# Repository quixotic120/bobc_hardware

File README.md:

Fork of bobc’s hardware projects branch for my variant of Ramps-FD. See readme inside Ramps-FD for more info

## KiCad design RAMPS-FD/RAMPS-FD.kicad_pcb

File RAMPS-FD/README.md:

remix of ramps-fd; originally by bobc: https://github.com/bobc/bobc_hardware/tree/master/RAMPS-FD

edit: got the first rev of the board back but there were some clearance issues and a few errors in the schematic. these have been revised and rev 2 is on order. I have to again promote bayareacircuits - the price is unbeatable if you have a .edu email and the boards are of good quality. The solder mask leaves a bit to be desired but for the cost I can’t complain, especially when UV curable mask for touchups can be had on eBay for next to nothing. I have also began configuring a version of repetier to accommodate the changes and additions in the pinout; this is also on my github

as of now this is untested! board on order; will test very soon

based on v2.a - wasn't able to find anything but the flawed v1 for sale and other due/32-bit electronics didn't support what I want to do. So I made my own
I dont believe I changed any pinouts so the ramps-fd v2.a selection in repetier should cover this board as well. I'll certainly double check this

changes made - 
board layout is completely new 

added dedicated 5v supply on board. I'm using a murata dc-dc converter that is excellent but a bit expensive (7-10 bucks); however it is pin compatible with any 7805 for lower cost (but significantly more heat). Also left in the option to use the due's 5v out but it's not sufficient for the extras I want

integrated the LCD connector board. Hate having an extra board hanging off and never use the ports for anything else. Lose several aux ports as a result.

6 stepper support (x,y,z,e0,e1,e2). Drivers are integrated to the board and are TMC2100/2130 (either will work). For the most part cooling should be okay but the board is a bit tight so some can't have all of their vias for heat dispersal. I don't know how bad this is but compared to the crap cooling on most stepper drivers I'm assuming it will be okay. I suck at PCB layout so this could probably be significantly improved. also could probably further remix to utilize DRV8825/a4988 for the extruders as I'd imagine the TMC drivers dont have much of a benefit there. This wouldnt necessarily make anything easier but would lower the cost of the board by a few dollars and be slightly easier to solder

added a second header for z axis in parallel for machines with two z steppers

with the exception of very few parts almost everything has been moved to SMD parts. Off the top of my head I'm pretty sure the only through hole components are the various pin headers for connection to Due, servos, lcd, etc, jacks for auto mini blade fuses, and the connectors for power connections. Ton of vias though so if you plan to manufacture this get ready for a serious headache.

adding a layer could probably improve the layout significantly but I'm shooting for very cheap manufacture. I have placed an order via http://store.bayareacircuits.com/student-special/ (need a student email (e.g. .edu) for discount) and with shipping and tax it was around 40 bucks for the prototype. Will report when it arrives. 

otherwise it is available via [oshpark](https://oshpark.com/shared_projects/LaipPQTx) @ 164.65+shipping for 3 (min order, ~55 per board) as of 3/30/16

GPLv3

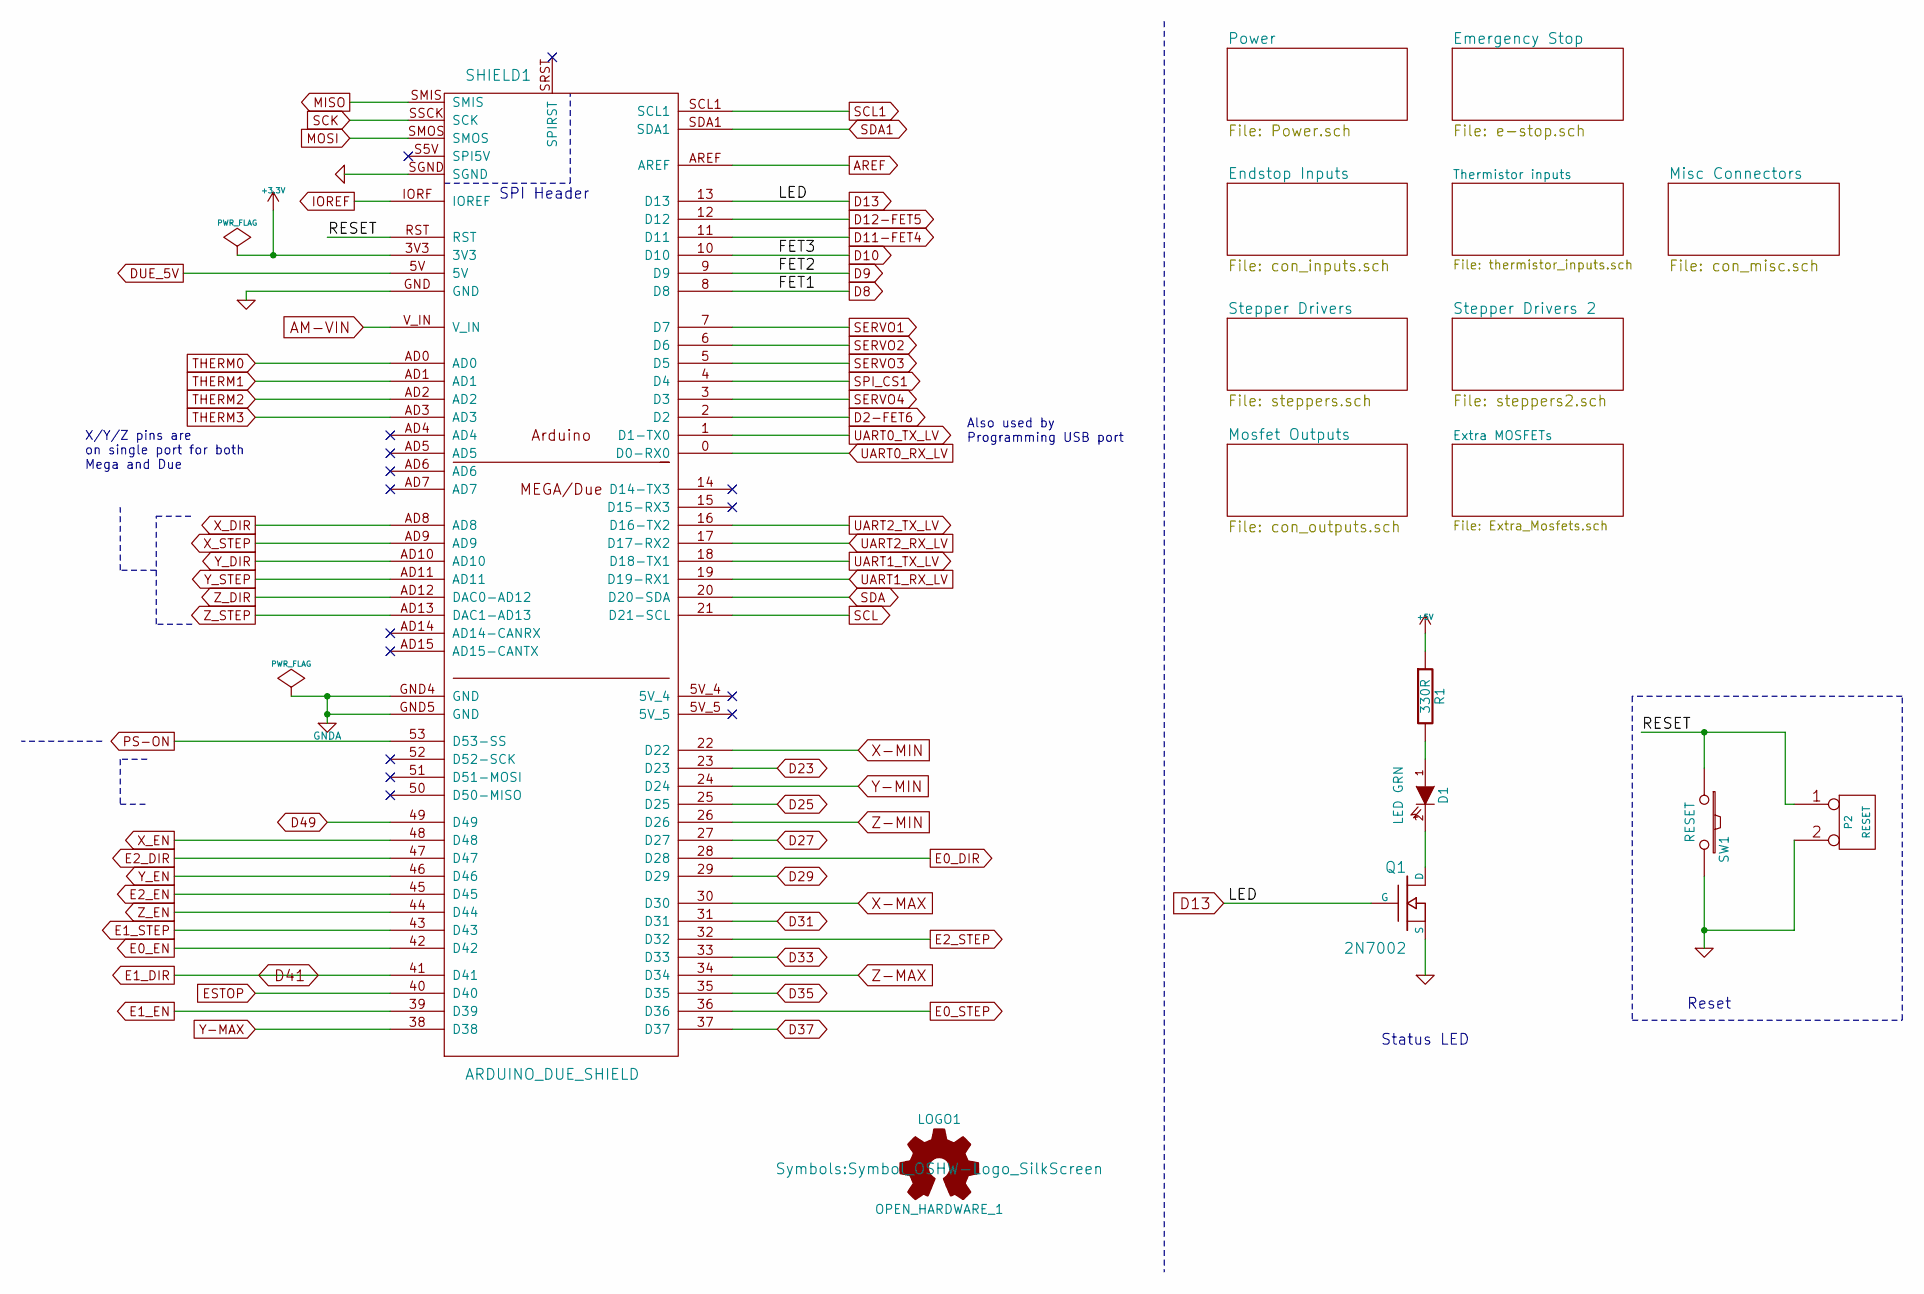
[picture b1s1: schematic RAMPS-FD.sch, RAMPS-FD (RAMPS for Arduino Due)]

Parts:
D1: LED GRN; LED_0805
LOGO1: OPEN_HARDWARE_1; Symbol_OSHW-Logo_SilkScreen
P2: RESET; Pin_Header_Straight_1x02
Q1: 2N7002; SOT-23_GDS
R1: 330R; R_0805
SHIELD1: ARDUINO_DUE_SHIELD; ARDUINO_DUE_RAMPS_SHIELD
SW1: RESET; SW_PUSH_SMALL

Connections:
+3V3: SHIELD1.3V3
/RESET: P2.1, SHIELD1.RST, SW1.1
AM-VIN: SHIELD1.V_IN; also elsewhere on the board
D2-FET6: SHIELD1.2 (D2); also elsewhere on the board
D8: SHIELD1.8 (D8); also elsewhere on the board
D9: SHIELD1.9 (D9); also elsewhere on the board
D10: SHIELD1.10 (D10); also elsewhere on the board
D11-FET4: SHIELD1.11 (D11); also elsewhere on the board
D12-FET5: SHIELD1.12 (D12); also elsewhere on the board
D13: Q1.G, SHIELD1.13 (D13)
D23: SHIELD1.23 (D23); also elsewhere on the board
D25: SHIELD1.25 (D25); also elsewhere on the board
D27: SHIELD1.27 (D27); also elsewhere on the board
D29: SHIELD1.29 (D29); also elsewhere on the board
D31: SHIELD1.31 (D31); also elsewhere on the board
D33: SHIELD1.33 (D33); also elsewhere on the board
D35: SHIELD1.35 (D35); also elsewhere on the board
D37: SHIELD1.37 (D37); also elsewhere on the board
D41: SHIELD1.41 (D41); also elsewhere on the board
D49: SHIELD1.49 (D49); also elsewhere on the board
DUE_5V: SHIELD1.5V; also elsewhere on the board
E0_DIR: SHIELD1.28 (D28); also elsewhere on the board
E0_EN: SHIELD1.42 (D42); also elsewhere on the board
E0_STEP: SHIELD1.36 (D36); also elsewhere on the board
E1_EN: SHIELD1.39 (D39); also elsewhere on the board
E1_STEP: SHIELD1.43 (D43); also elsewhere on the board
E2_DIR: SHIELD1.47 (D47); also elsewhere on the board
E2_EN: SHIELD1.45 (D45); also elsewhere on the board
E2_STEP: SHIELD1.32 (D32); also elsewhere on the board
ESTOP: SHIELD1.40 (D40); also elsewhere on the board
FD_5V: R1.1; also elsewhere on the board
GNDA: SHIELD1.GND4 (GND), SHIELD1.GND5 (GND); also elsewhere on the board
IOREF: SHIELD1.IORF (IOREF); also elsewhere on the board
MISO: SHIELD1.SMIS; also elsewhere on the board
MOSI: SHIELD1.SMOS; also elsewhere on the board
unnamed: D1.1 (A), R1.2
unnamed: D1.2 (K), Q1.D
PS-ON: SHIELD1.53 (D53-SS); also elsewhere on the board
SCK: SHIELD1.SSCK (SCK); also elsewhere on the board
SCL: SHIELD1.21 (D21-SCL); also elsewhere on the board
SCL1: SHIELD1.SCL1; also elsewhere on the board
SDA: SHIELD1.20 (D20-SDA); also elsewhere on the board
SDA1: SHIELD1.SDA1; also elsewhere on the board
SERVO1: SHIELD1.7 (D7); also elsewhere on the board
SERVO2: SHIELD1.6 (D6); also elsewhere on the board
SERVO3: SHIELD1.5 (D5); also elsewhere on the board
SERVO4: SHIELD1.3 (D3); also elsewhere on the board
SPI_CS1: SHIELD1.4 (D4); also elsewhere on the board
THERM0: SHIELD1.AD0; also elsewhere on the board
THERM1: SHIELD1.AD1; also elsewhere on the board
THERM2: SHIELD1.AD2; also elsewhere on the board
THERM3: SHIELD1.AD3; also elsewhere on the board
UART0_RX_LV: SHIELD1.0 (D0-RX0); also elsewhere on the board
UART0_TX_LV: SHIELD1.1 (D1-TX0); also elsewhere on the board
UART1_RX_LV: SHIELD1.19 (D19-RX1); also elsewhere on the board
UART1_TX_LV: SHIELD1.18 (D18-TX1); also elsewhere on the board
UART2_RX_LV: SHIELD1.17 (D17-RX2); also elsewhere on the board
UART2_TX_LV: SHIELD1.16 (D16-TX2); also elsewhere on the board
X-MAX: SHIELD1.30 (D30); also elsewhere on the board
X-MIN: SHIELD1.22 (D22); also elsewhere on the board
X_DIR: SHIELD1.AD8; also elsewhere on the board
X_EN: SHIELD1.48 (D48); also elsewhere on the board
X_STEP: SHIELD1.AD9; also elsewhere on the board
Y-MAX: SHIELD1.38 (D38); also elsewhere on the board
Y-MIN: SHIELD1.24 (D24); also elsewhere on the board
Y_DIR: SHIELD1.AD10; also elsewhere on the board
Y_EN: SHIELD1.46 (D46); also elsewhere on the board
Y_STEP: SHIELD1.AD11; also elsewhere on the board
Z-MAX: SHIELD1.34 (D34); also elsewhere on the board
Z-MIN: SHIELD1.26 (D26); also elsewhere on the board
Z_DIR: SHIELD1.AD12 (DAC0-AD12); also elsewhere on the board
Z_EN: SHIELD1.44 (D44); also elsewhere on the board
Z_STEP: SHIELD1.AD13 (DAC1-AD13); also elsewhere on the board

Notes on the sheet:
Also used by Programming USB port
X/Y/Z pins are on single port for both Mega and Due
Reset
Status LED
SPI Header

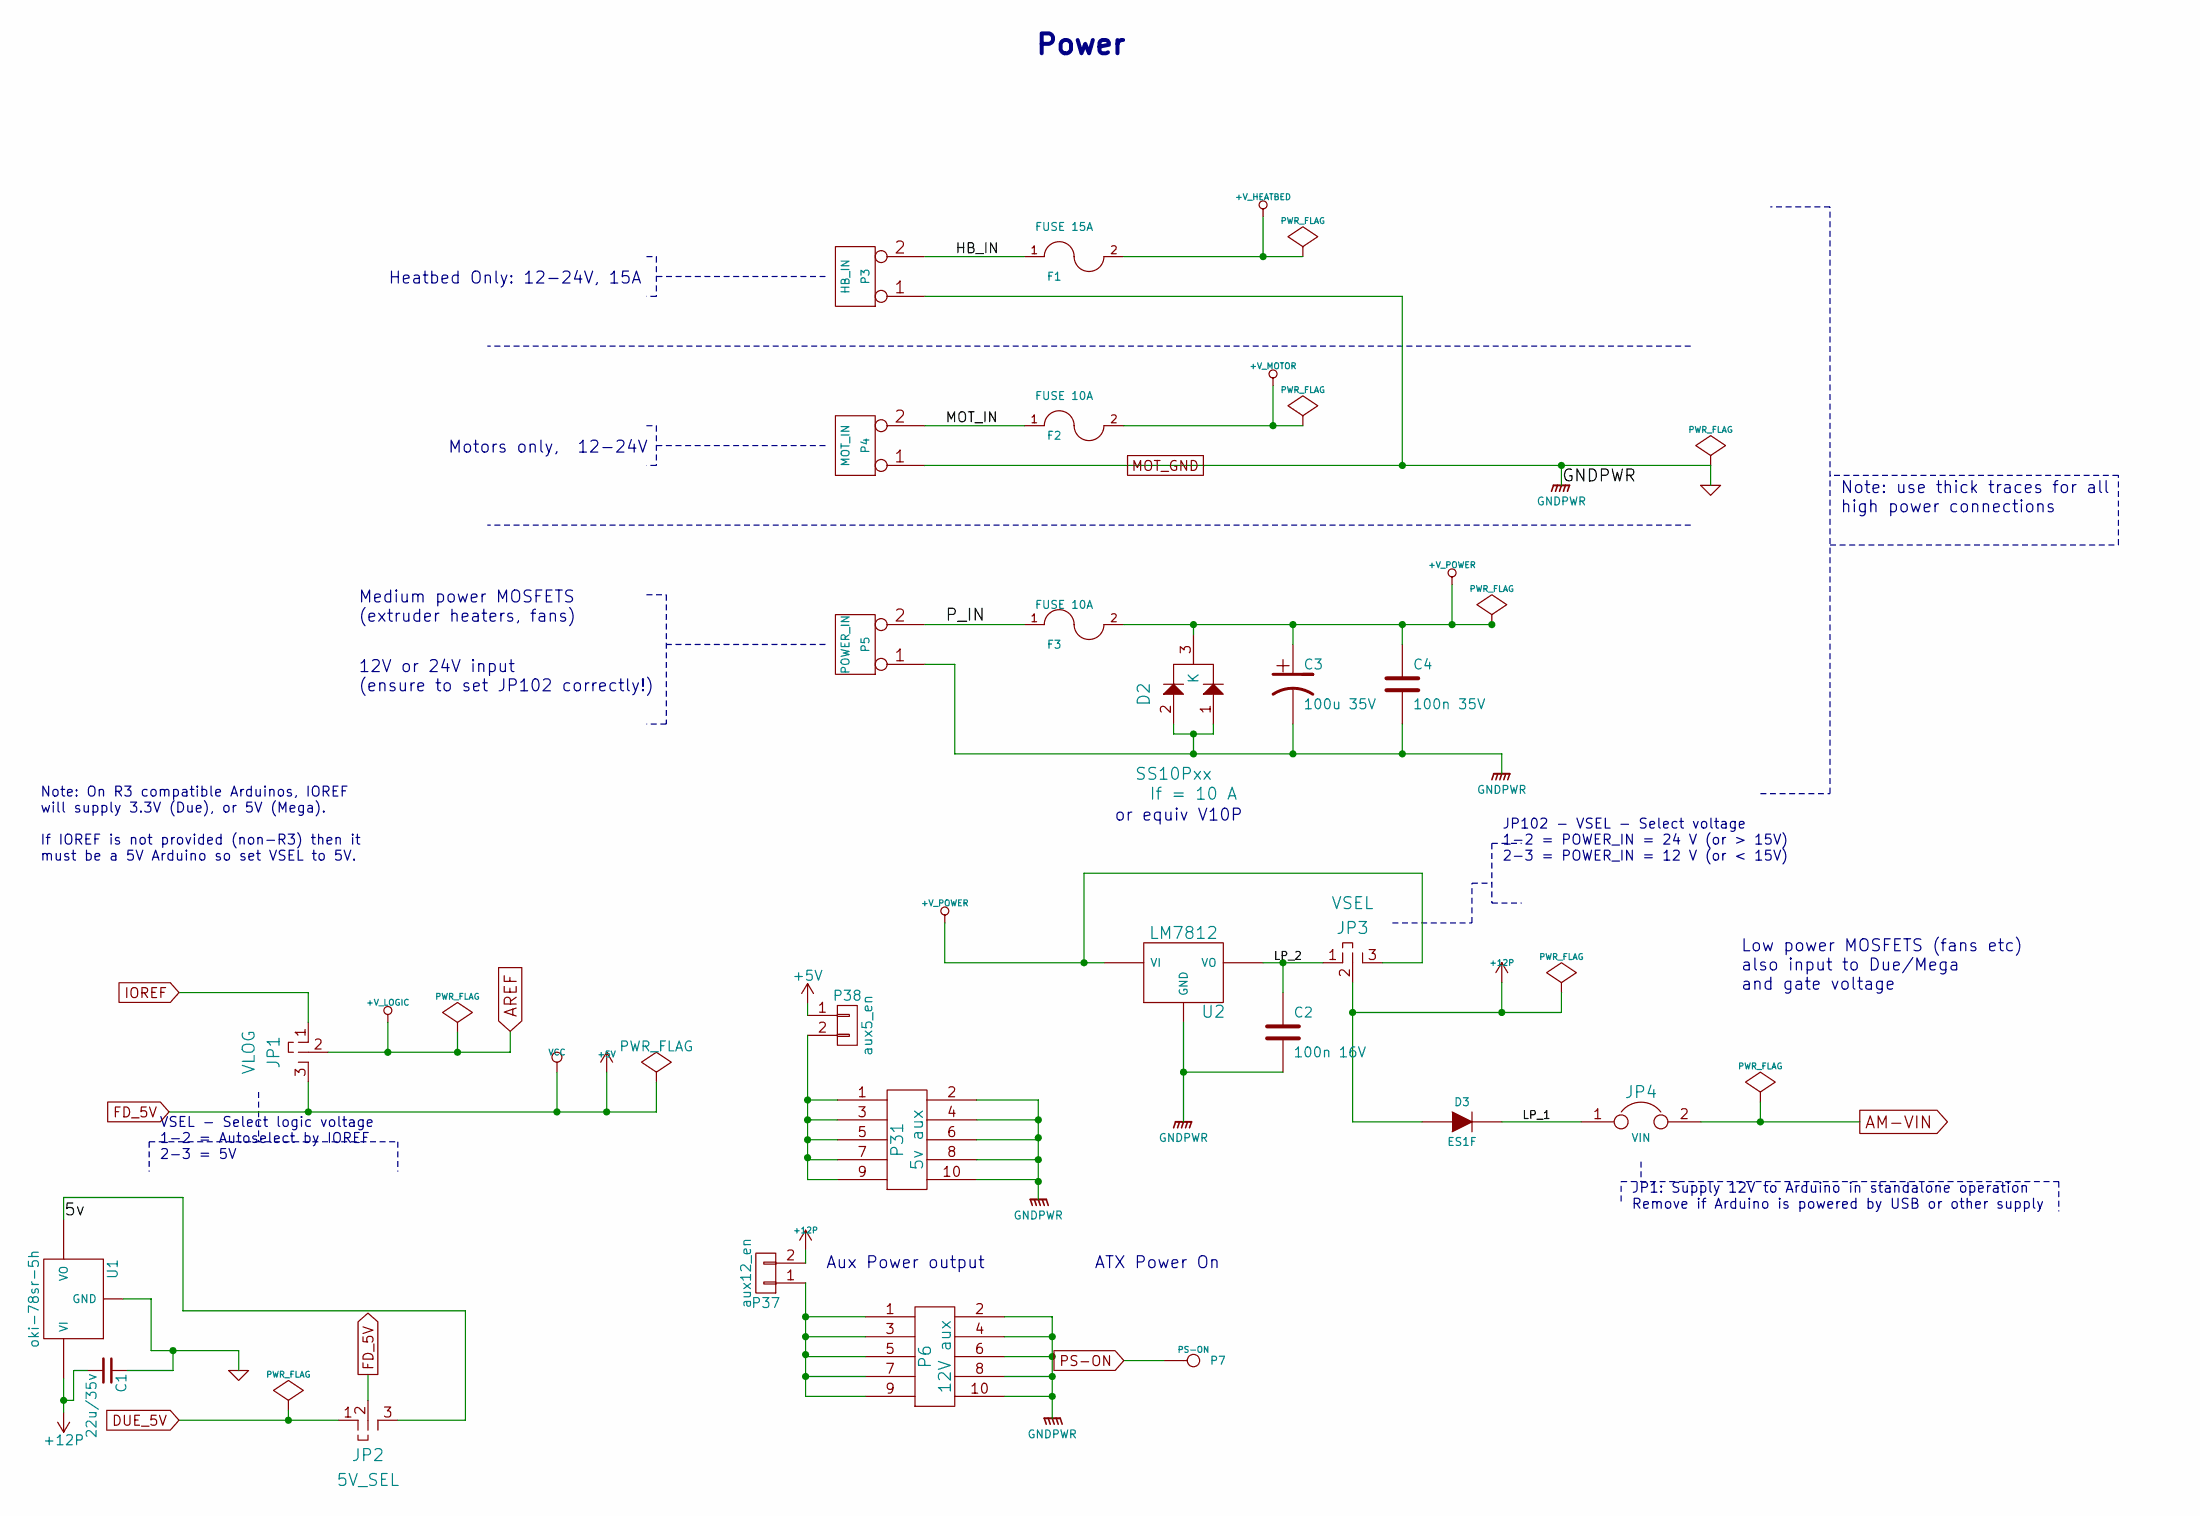
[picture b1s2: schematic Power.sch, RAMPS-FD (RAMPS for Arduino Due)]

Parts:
C1: 22u/35v; C_0805
C2: 100n 16V; C_0805
C3: 100u 35V; c_elec_6.3x7.7
C4: 100n 35V; C_0805
D2: SS10Pxx; TO-277A
D3: ES1F; DO-214AB
F1: FUSE 15A; FUSE-MINI-AUTO
F2, F3: FUSE 10A; FUSE-MINI-AUTO
JP1: VLOG; Pin_Header_Straight_1x03
JP2: 5V_SEL; Pin_Header_Straight_1x03
JP3: VSEL; Pin_Header_Straight_1x03
JP4: VIN; Pin_Header_Straight_1x02
P3: HB_IN; 2p-conn-5,08
P4: MOT_IN; 2p-conn-5,08
P5: POWER_IN; 2p-conn-5,08
P6: 12V aux; Pin_Header_Straight_2x05
P7: PS-ON; Pin_Header_Straight_1x01
P31: 5v aux; Pin_Header_Straight_2x05
P37: aux12_en; Pin_Header_Straight_1x02
P38: aux5_en; Pin_Header_Straight_1x02
U1: oki-78sr-5h; TO-220_Neutral123_Horizontal_OKI_Mod
U2: LM7812; TO-252-2Lead_edit

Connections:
+12P: C1.2, D3.1 (A), JP3.2, P37.2, U1.VI; also elsewhere on the board
+V_HEATBED: F1.2; also elsewhere on the board
+V_MOTOR: F2.2; also elsewhere on the board
+V_POWER: C3.1, C4.1, D2.3 (K), F3.2, JP3.3, U2.VI; also elsewhere on the board
/Power/5v: JP2.3, U1.VO
/Power/HB_IN: F1.1, P3.2 (PM)
/Power/LP_1: D3.2 (K), JP4.1
/Power/LP_2: C2.1, JP3.1, U2.VO
/Power/MOT_IN: F2.1, P4.2 (PM)
/Power/P_IN: F3.1, P5.2 (PM)
AM-VIN: JP4.2; also elsewhere on the board
DUE_5V: JP2.1; also elsewhere on the board
FD_5V: JP1.3, JP2.2, P38.1; also elsewhere on the board
IOREF: JP1.1; also elsewhere on the board
unnamed: P31.1, P31.3, P31.5, P31.7, P31.9, P38.2
unnamed: P6.1, P6.3, P6.5, P6.7, P6.9, P37.1
PS-ON: P7.1; also elsewhere on the board

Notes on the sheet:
JP102 - VSEL - Select voltage 1-2 = POWER_IN = 24 V (or > 15V) 2-3 = POWER_IN = 12 V (or < 15V)
Low power MOSFETS (fans etc) also input to Due/Mega and gate voltage
Aux Power output
VSEL - Select logic voltage 1-2 = Autoselect by IOREF 2-3 = 5V
Note: On R3 compatible Arduinos, IOREF will supply 3.3V (Due), or 5V (Mega). If IOREF is not provided (non-R3) then it must be a 5V Arduino so set VSEL to 5V.
Medium power MOSFETS (extruder heaters, fans)
Heatbed Only: 12-24V, 15A
Motors only, 12-24V
Power
JP1: Supply 12V to Arduino in standalone operation Remove if Arduino is powered by USB or other supply
Note: use thick traces for all high power connections
12V or 24V input (ensure to set JP102 correctly!)
ATX Power On
or equiv V10P

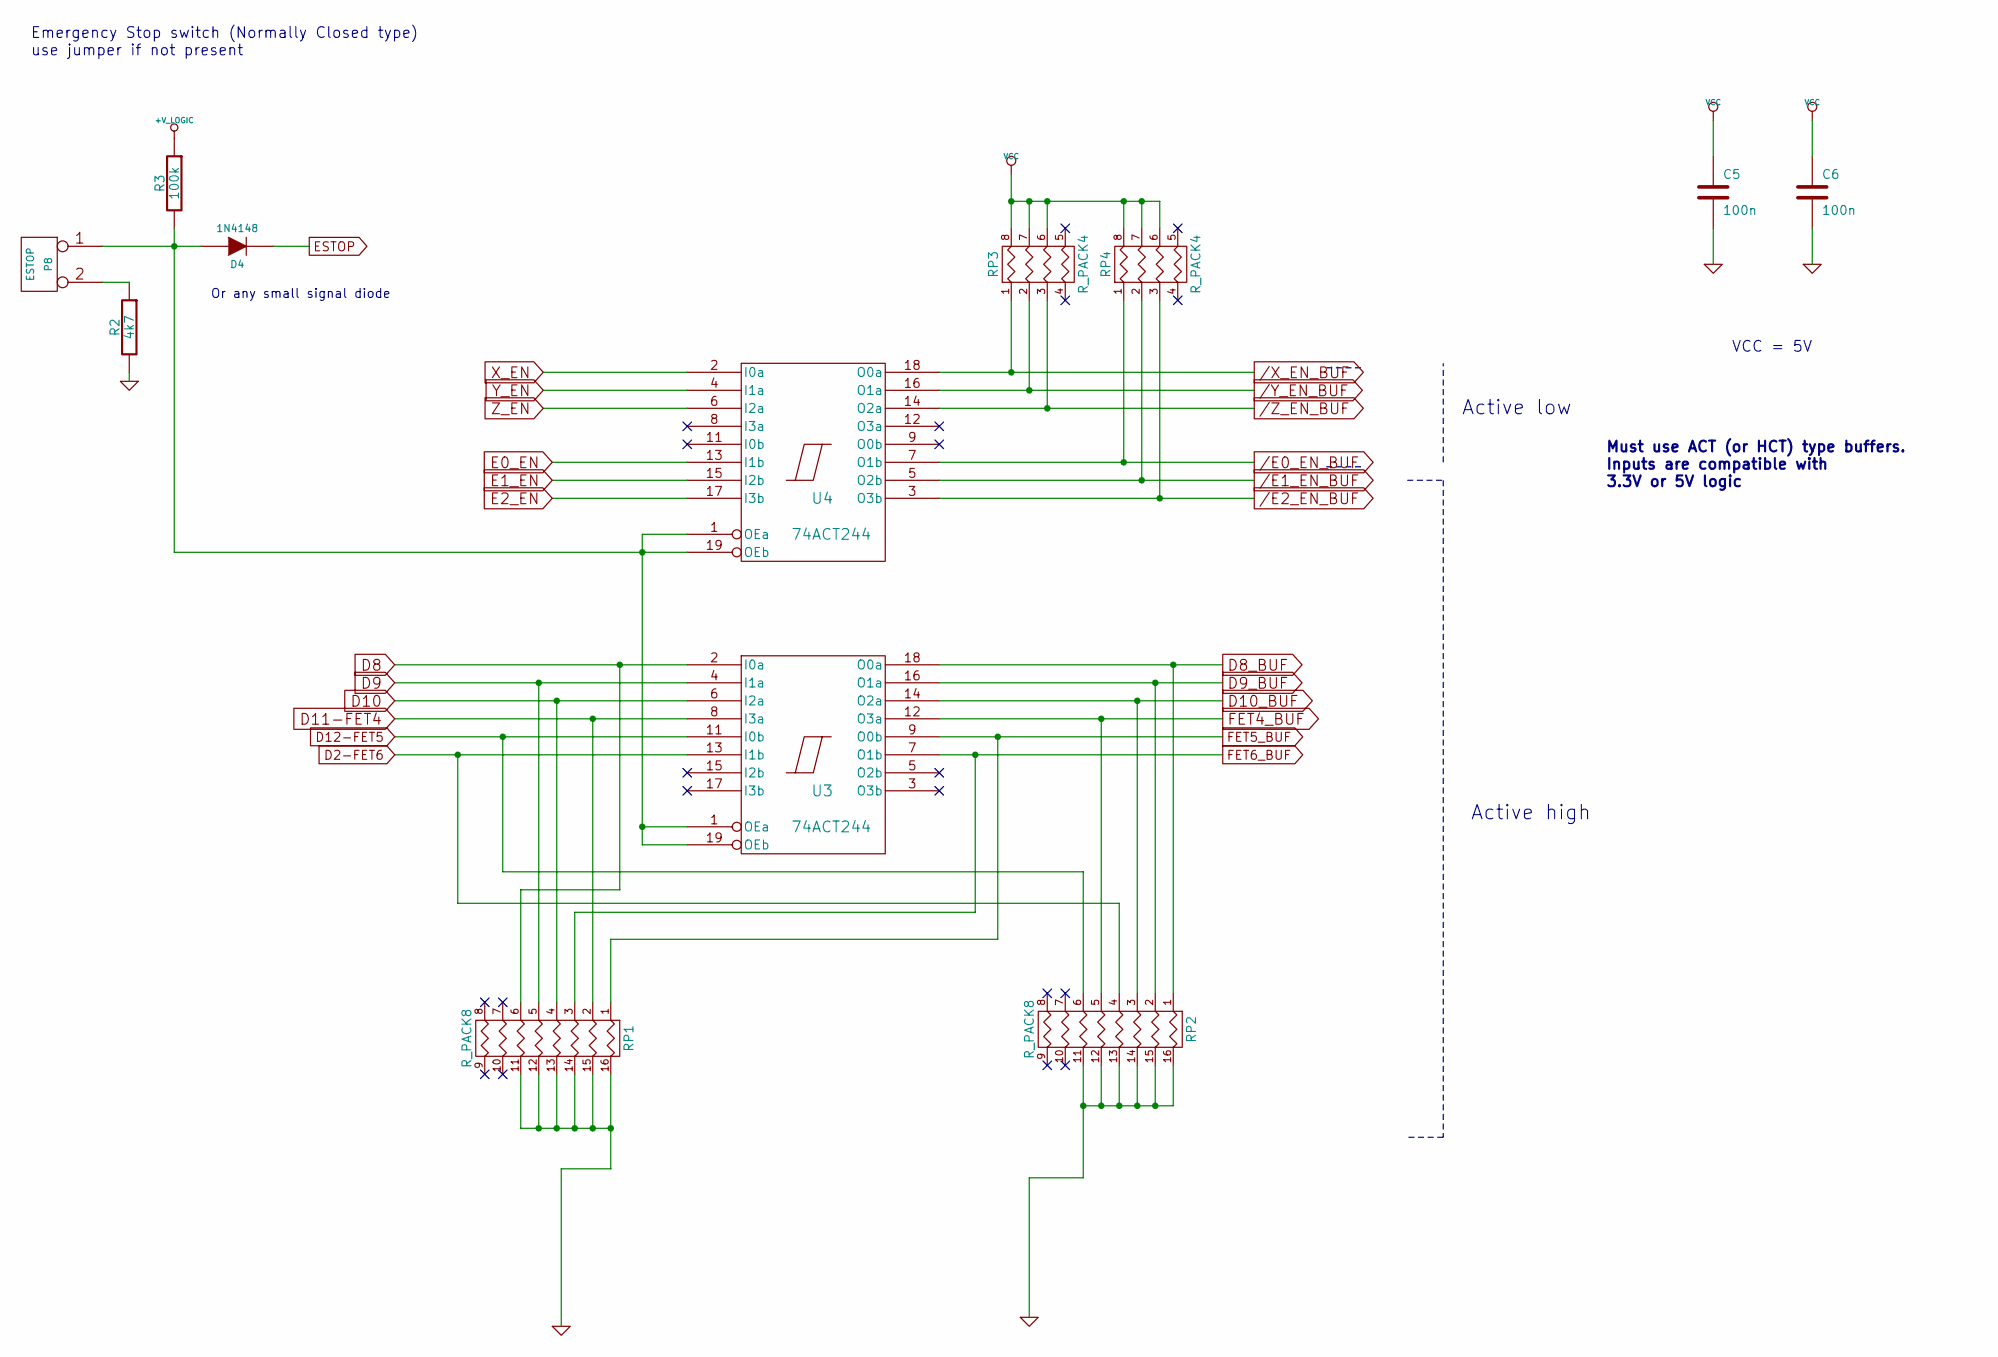
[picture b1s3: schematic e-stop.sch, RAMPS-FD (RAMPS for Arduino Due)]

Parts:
C5, C6: 100n; C_0805
D4: 1N4148; SOD-323
P8: ESTOP; Socket_MOLEX-KK-RM2-54mm_Lock_2pin_straight
R2: 4k7; R_0805
R3: 100k; R_0805
RP1, RP2: R_PACK8; R_Cat16-8
RP3, RP4: R_PACK4; R_Cat16-4
U3, U4: 74ACT244; TSSOP-20_4.4x6.5mm_Pitch0.65mm

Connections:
/E0_EN_BUF: RP4.1, U4.7 (O1b); also elsewhere on the board
/E1_EN_BUF: RP4.2, U4.5 (O2b); also elsewhere on the board
/E2_EN_BUF: RP4.3, U4.3 (O3b); also elsewhere on the board
/X_EN_BUF: RP3.1, U4.18 (O0a); also elsewhere on the board
/Y_EN_BUF: RP3.2, U4.16 (O1a); also elsewhere on the board
/Z_EN_BUF: RP3.3, U4.14 (O2a); also elsewhere on the board
D2-FET6: RP2.4, U3.13 (I1b); also elsewhere on the board
D8: RP1.6, U3.2 (I0a); also elsewhere on the board
D8_BUF: RP2.1, U3.18 (O0a); also elsewhere on the board
D9: RP1.5, U3.4 (I1a); also elsewhere on the board
D9_BUF: RP2.2, U3.16 (O1a); also elsewhere on the board
D10: RP1.4, U3.6 (I2a); also elsewhere on the board
D10_BUF: RP2.3, U3.14 (O2a); also elsewhere on the board
D11-FET4: RP1.2, U3.8 (I3a); also elsewhere on the board
D12-FET5: RP2.6, U3.11 (I0b); also elsewhere on the board
E0_EN: U4.13 (I1b); also elsewhere on the board
E1_EN: U4.15 (I2b); also elsewhere on the board
E2_EN: U4.17 (I3b); also elsewhere on the board
ESTOP: D4.2 (K); also elsewhere on the board
FD_5V: C5.1, C6.1, RP3.6 (R3), RP3.7 (R2), RP3.8 (R1), RP4.6 (R3), RP4.7 (R2), RP4.8 (R1), U3.20 (VCC), U4.20 (VCC); also elsewhere on the board
FET4_BUF: RP2.5, U3.12 (O3a); also elsewhere on the board
FET5_BUF: RP1.1, U3.9 (O0b); also elsewhere on the board
FET6_BUF: RP1.3, U3.7 (O1b); also elsewhere on the board
unnamed: D4.1 (A), P8.1, R3.2, U3.1 (OEa), U3.19 (OEb), U4.1 (OEa), U4.19 (OEb)
unnamed: P8.2 (PM), R2.1
X_EN: U4.2 (I0a); also elsewhere on the board
Y_EN: U4.4 (I1a); also elsewhere on the board
Z_EN: U4.6 (I2a); also elsewhere on the board

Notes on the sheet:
Emergency Stop switch (Normally Closed type) use jumper if not present
Or any small signal diode
Active low
Active high
VCC = 5V
Must use ACT (or HCT) type buffers. Inputs are compatible with 3.3V or 5V logic

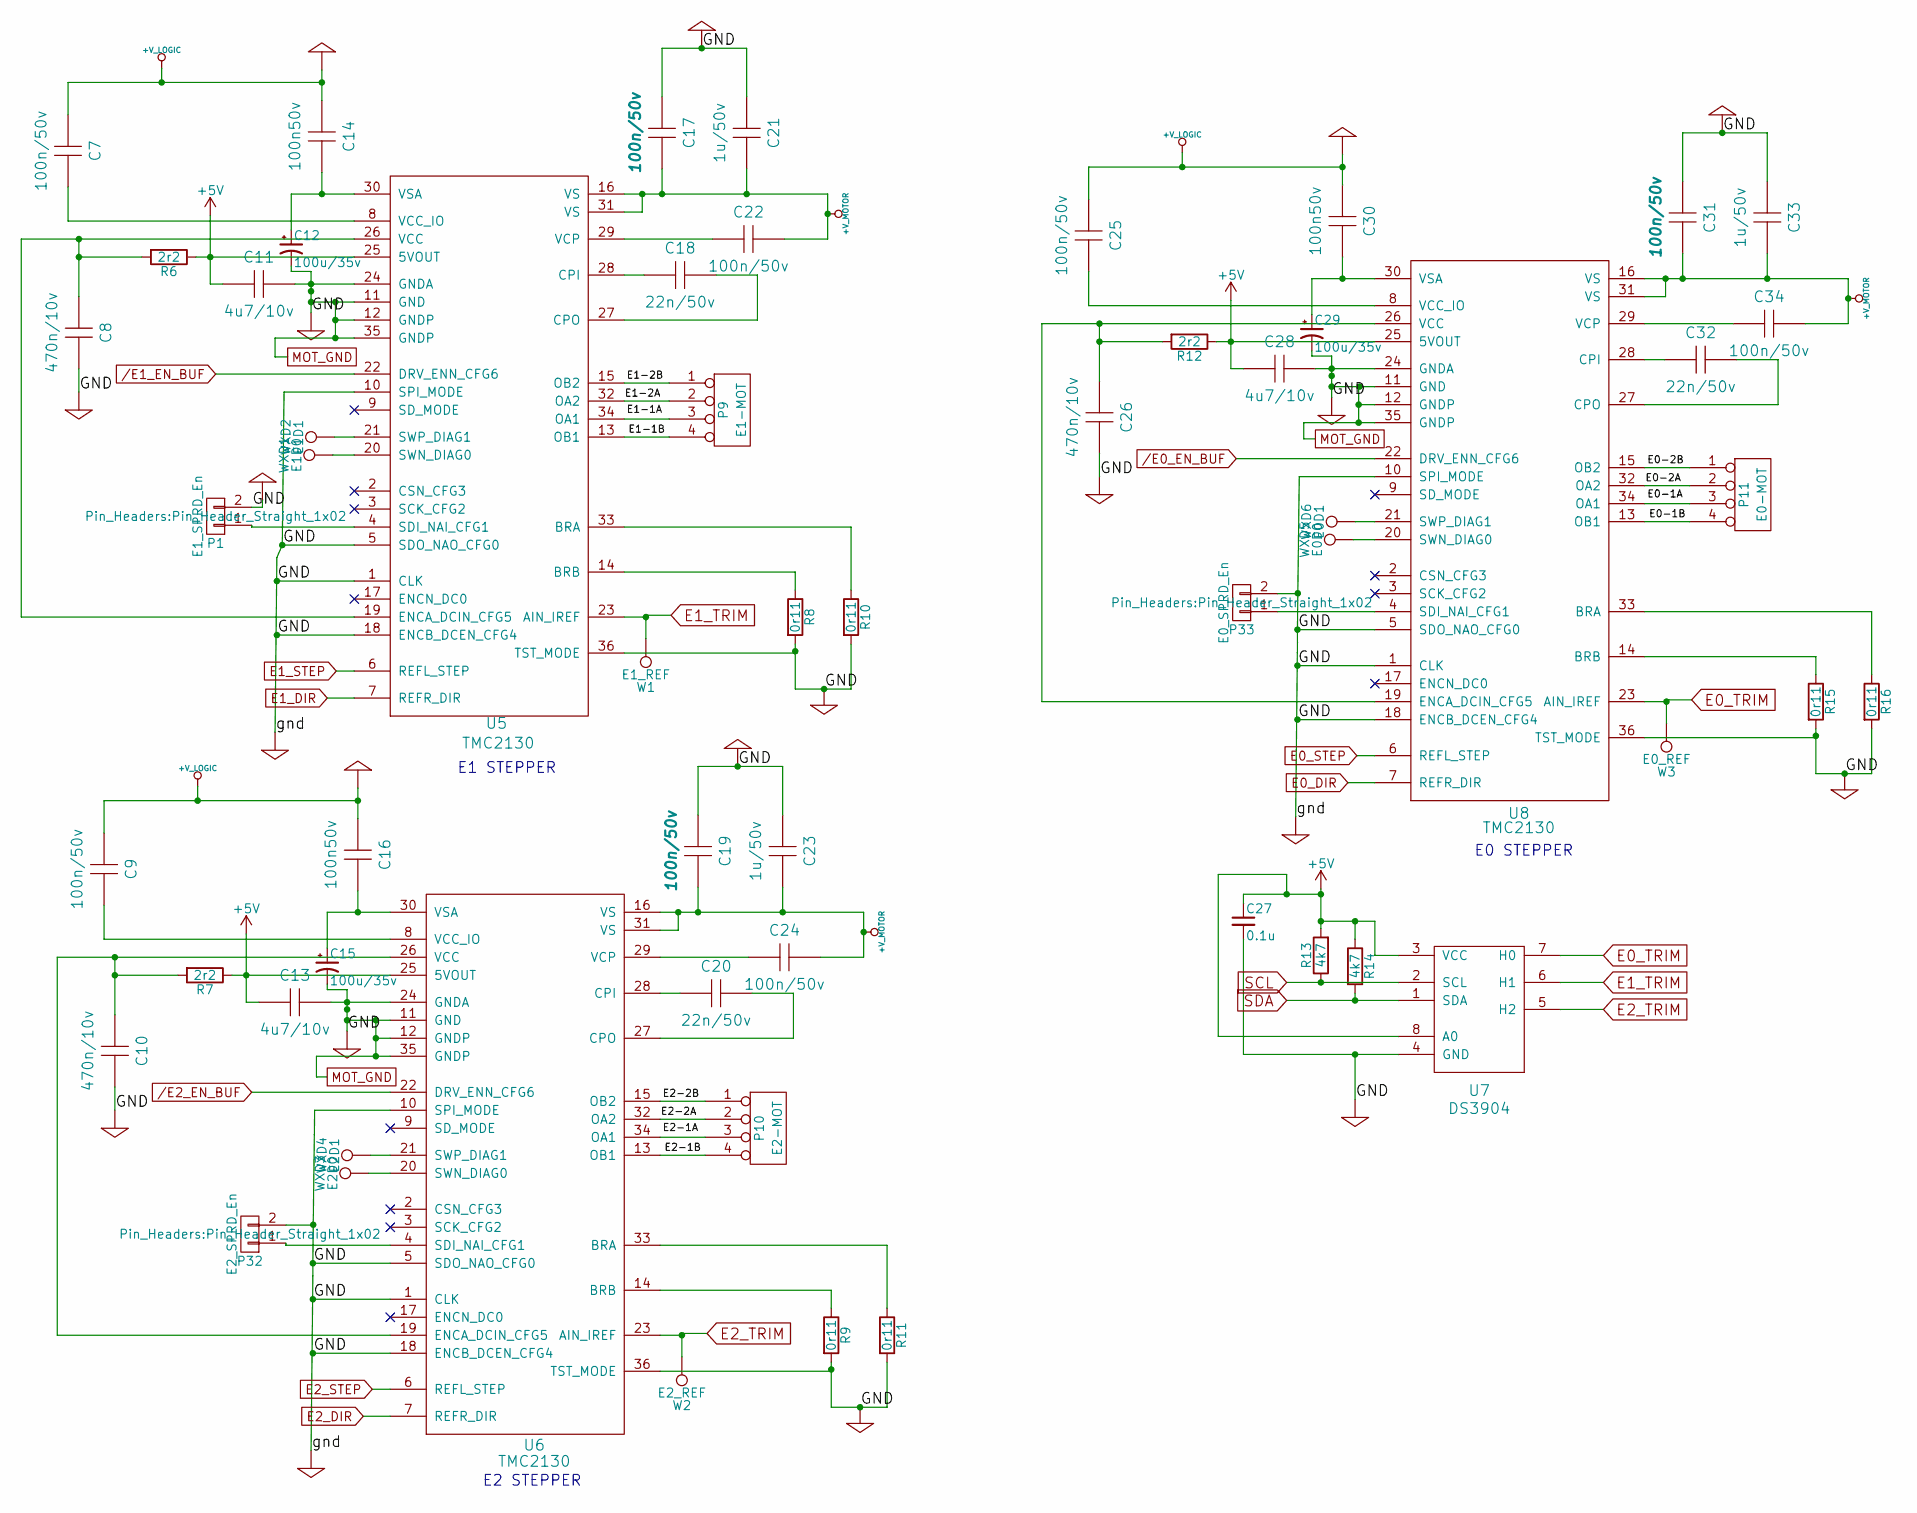
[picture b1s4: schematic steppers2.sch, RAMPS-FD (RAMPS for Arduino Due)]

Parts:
C7, C9, C17, C19, C22, C24, C25, C31, C34: 100n/50v; C_0805
C8, C10, C26: 470n/10v; C_0805
C11, C13, C28: 4u7/10v; C_0805
C12, C15, C29: 100u/35v; c_elec_6.3x7.7
C14, C16, C30: 100n50v; C_0805
C18, C20, C32: 22n/50v; C_0805
C21, C23, C33: 1u/50v; C_0805
C27: 0.1u; C_0805
P1: E1_SPRD_En; Pin_Header_Straight_1x02
P9: E1-MOT; Socket_MOLEX-KK-RM2-54mm_Lock_4pin_straight
P10: E2-MOT; Socket_MOLEX-KK-RM2-54mm_Lock_4pin_straight
P11: E0-MOT; Socket_MOLEX-KK-RM2-54mm_Lock_4pin_straight
P32: E2_SPRD_En; Pin_Header_Straight_1x02
P33: E0_SPRD_En; Pin_Header_Straight_1x02
R6, R7, R12: 2r2; R_0805
R8, R9, R10, R11, R15, R16: 0r11; R_0805
R13, R14: 4k7; R_0805
U5, U6, U8: TMC2130; QFN-36-1EP_5x6mm_Pitch0.5mm
U7: DS3904; MSOP-8-1EP_3x3mm_Pitch0.65mm
W1: E1_REF; SolderWirePad_single_0-8mmDrill
W2: E2_REF; SolderWirePad_single_0-8mmDrill
W3: E0_REF; SolderWirePad_single_0-8mmDrill
WXD1: E1D0; SolderWirePad_single_0-8mmDrill
WXD2: E1D1; SolderWirePad_single_0-8mmDrill
WXD3: E2D0; SolderWirePad_single_0-8mmDrill
WXD4: E2D1; SolderWirePad_single_0-8mmDrill
WXD5: E0D0; SolderWirePad_single_0-8mmDrill
WXD6: E0D1; SolderWirePad_single_0-8mmDrill

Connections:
+V_MOTOR: C17.2, C19.2, C21.2, C22.2, C23.2, C24.2, C31.2, C33.2, C34.2, U5.16 (VS), U5.31 (VS), U6.16 (VS), U6.31 (VS), U8.16 (VS), U8.31 (VS); also elsewhere on the board
/E0_EN_BUF: U8.22 (DRV_ENN_CFG6); also elsewhere on the board
/E1_EN_BUF: U5.22 (DRV_ENN_CFG6); also elsewhere on the board
/E2_EN_BUF: U6.22 (DRV_ENN_CFG6); also elsewhere on the board
D41: U5.7 (REFR_DIR); also elsewhere on the board
E0_DIR: U8.7 (REFR_DIR); also elsewhere on the board
E0_STEP: U8.6 (REFL_STEP); also elsewhere on the board
E0_TRIM: U7.7 (H0), U8.23 (AIN_IREF), W3.1
E1_STEP: U5.6 (REFL_STEP); also elsewhere on the board
E1_TRIM: U5.23 (AIN_IREF), U7.6 (H1), W1.1
E2_DIR: U6.7 (REFR_DIR); also elsewhere on the board
E2_STEP: U6.6 (REFL_STEP); also elsewhere on the board
E2_TRIM: U6.23 (AIN_IREF), U7.5 (H2), W2.1
FD_5V: C27.1, R13.2, R14.1, U7.3 (VCC), U7.8 (A0); also elsewhere on the board
unnamed: C7.2, U5.8 (VCC_IO)
unnamed: C8.1, R6.2, U5.19 (ENCA_DCIN_CFG5), U5.26 (VCC)
unnamed: C9.2, U6.8 (VCC_IO)
unnamed: C10.1, R7.2, U6.19 (ENCA_DCIN_CFG5), U6.26 (VCC)
unnamed: C11.1, R6.1, U5.25 (5VOUT)
unnamed: C12.1, C14.2, U5.30 (VSA)
unnamed: C13.1, R7.1, U6.25 (5VOUT)
unnamed: C15.1, C16.2, U6.30 (VSA)
unnamed: C18.1, U5.28 (CPI)
unnamed: C18.2, U5.27 (CPO)
unnamed: C20.1, U6.28 (CPI)
unnamed: C20.2, U6.27 (CPO)
unnamed: C22.1, U5.29 (VCP)
unnamed: C24.1, U6.29 (VCP)
unnamed: C25.2, U8.8 (VCC_IO)
unnamed: C26.1, R12.2, U8.19 (ENCA_DCIN_CFG5), U8.26 (VCC)
unnamed: C28.1, R12.1, U8.25 (5VOUT)
unnamed: C29.1, C30.2, U8.30 (VSA)
unnamed: C32.1, U8.28 (CPI)
unnamed: C32.2, U8.27 (CPO)
unnamed: C34.1, U8.29 (VCP)
unnamed: P1.1, U5.4 (SDI_NAI_CFG1)
unnamed: P9.1, U5.15 (OB2)
unnamed: P9.2, U5.32 (OA2)
unnamed: P9.3, U5.34 (OA1)
unnamed: P9.4, U5.13 (OB1)
unnamed: P10.1, U6.15 (OB2)
unnamed: P10.2, U6.32 (OA2)
unnamed: P10.3, U6.34 (OA1)
unnamed: P10.4, U6.13 (OB1)
unnamed: P11.1, U8.15 (OB2)
unnamed: P11.2, U8.32 (OA2)
unnamed: P11.3, U8.34 (OA1)
unnamed: P11.4, U8.13 (OB1)
unnamed: P32.1, U6.4 (SDI_NAI_CFG1)
unnamed: P33.1, U8.4 (SDI_NAI_CFG1)
unnamed: R8.1, U5.14 (BRB)
unnamed: R9.1, U6.14 (BRB)
unnamed: R10.1, U5.33 (BRA)
unnamed: R11.1, U6.33 (BRA)
unnamed: R15.1, U8.14 (BRB)
unnamed: R16.1, U8.33 (BRA)
unnamed: U5.20 (SWN_DIAG0), WXD1.1
unnamed: U5.21 (SWP_DIAG1), WXD2.1
unnamed: U6.20 (SWN_DIAG0), WXD3.1
unnamed: U6.21 (SWP_DIAG1), WXD4.1
unnamed: U8.20 (SWN_DIAG0), WXD5.1
unnamed: U8.21 (SWP_DIAG1), WXD6.1
SCL: R13.1, U7.2 (SCL); also elsewhere on the board
SDA: R14.2, U7.1 (SDA); also elsewhere on the board

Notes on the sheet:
E0 STEPPER
E1 STEPPER
E2 STEPPER
